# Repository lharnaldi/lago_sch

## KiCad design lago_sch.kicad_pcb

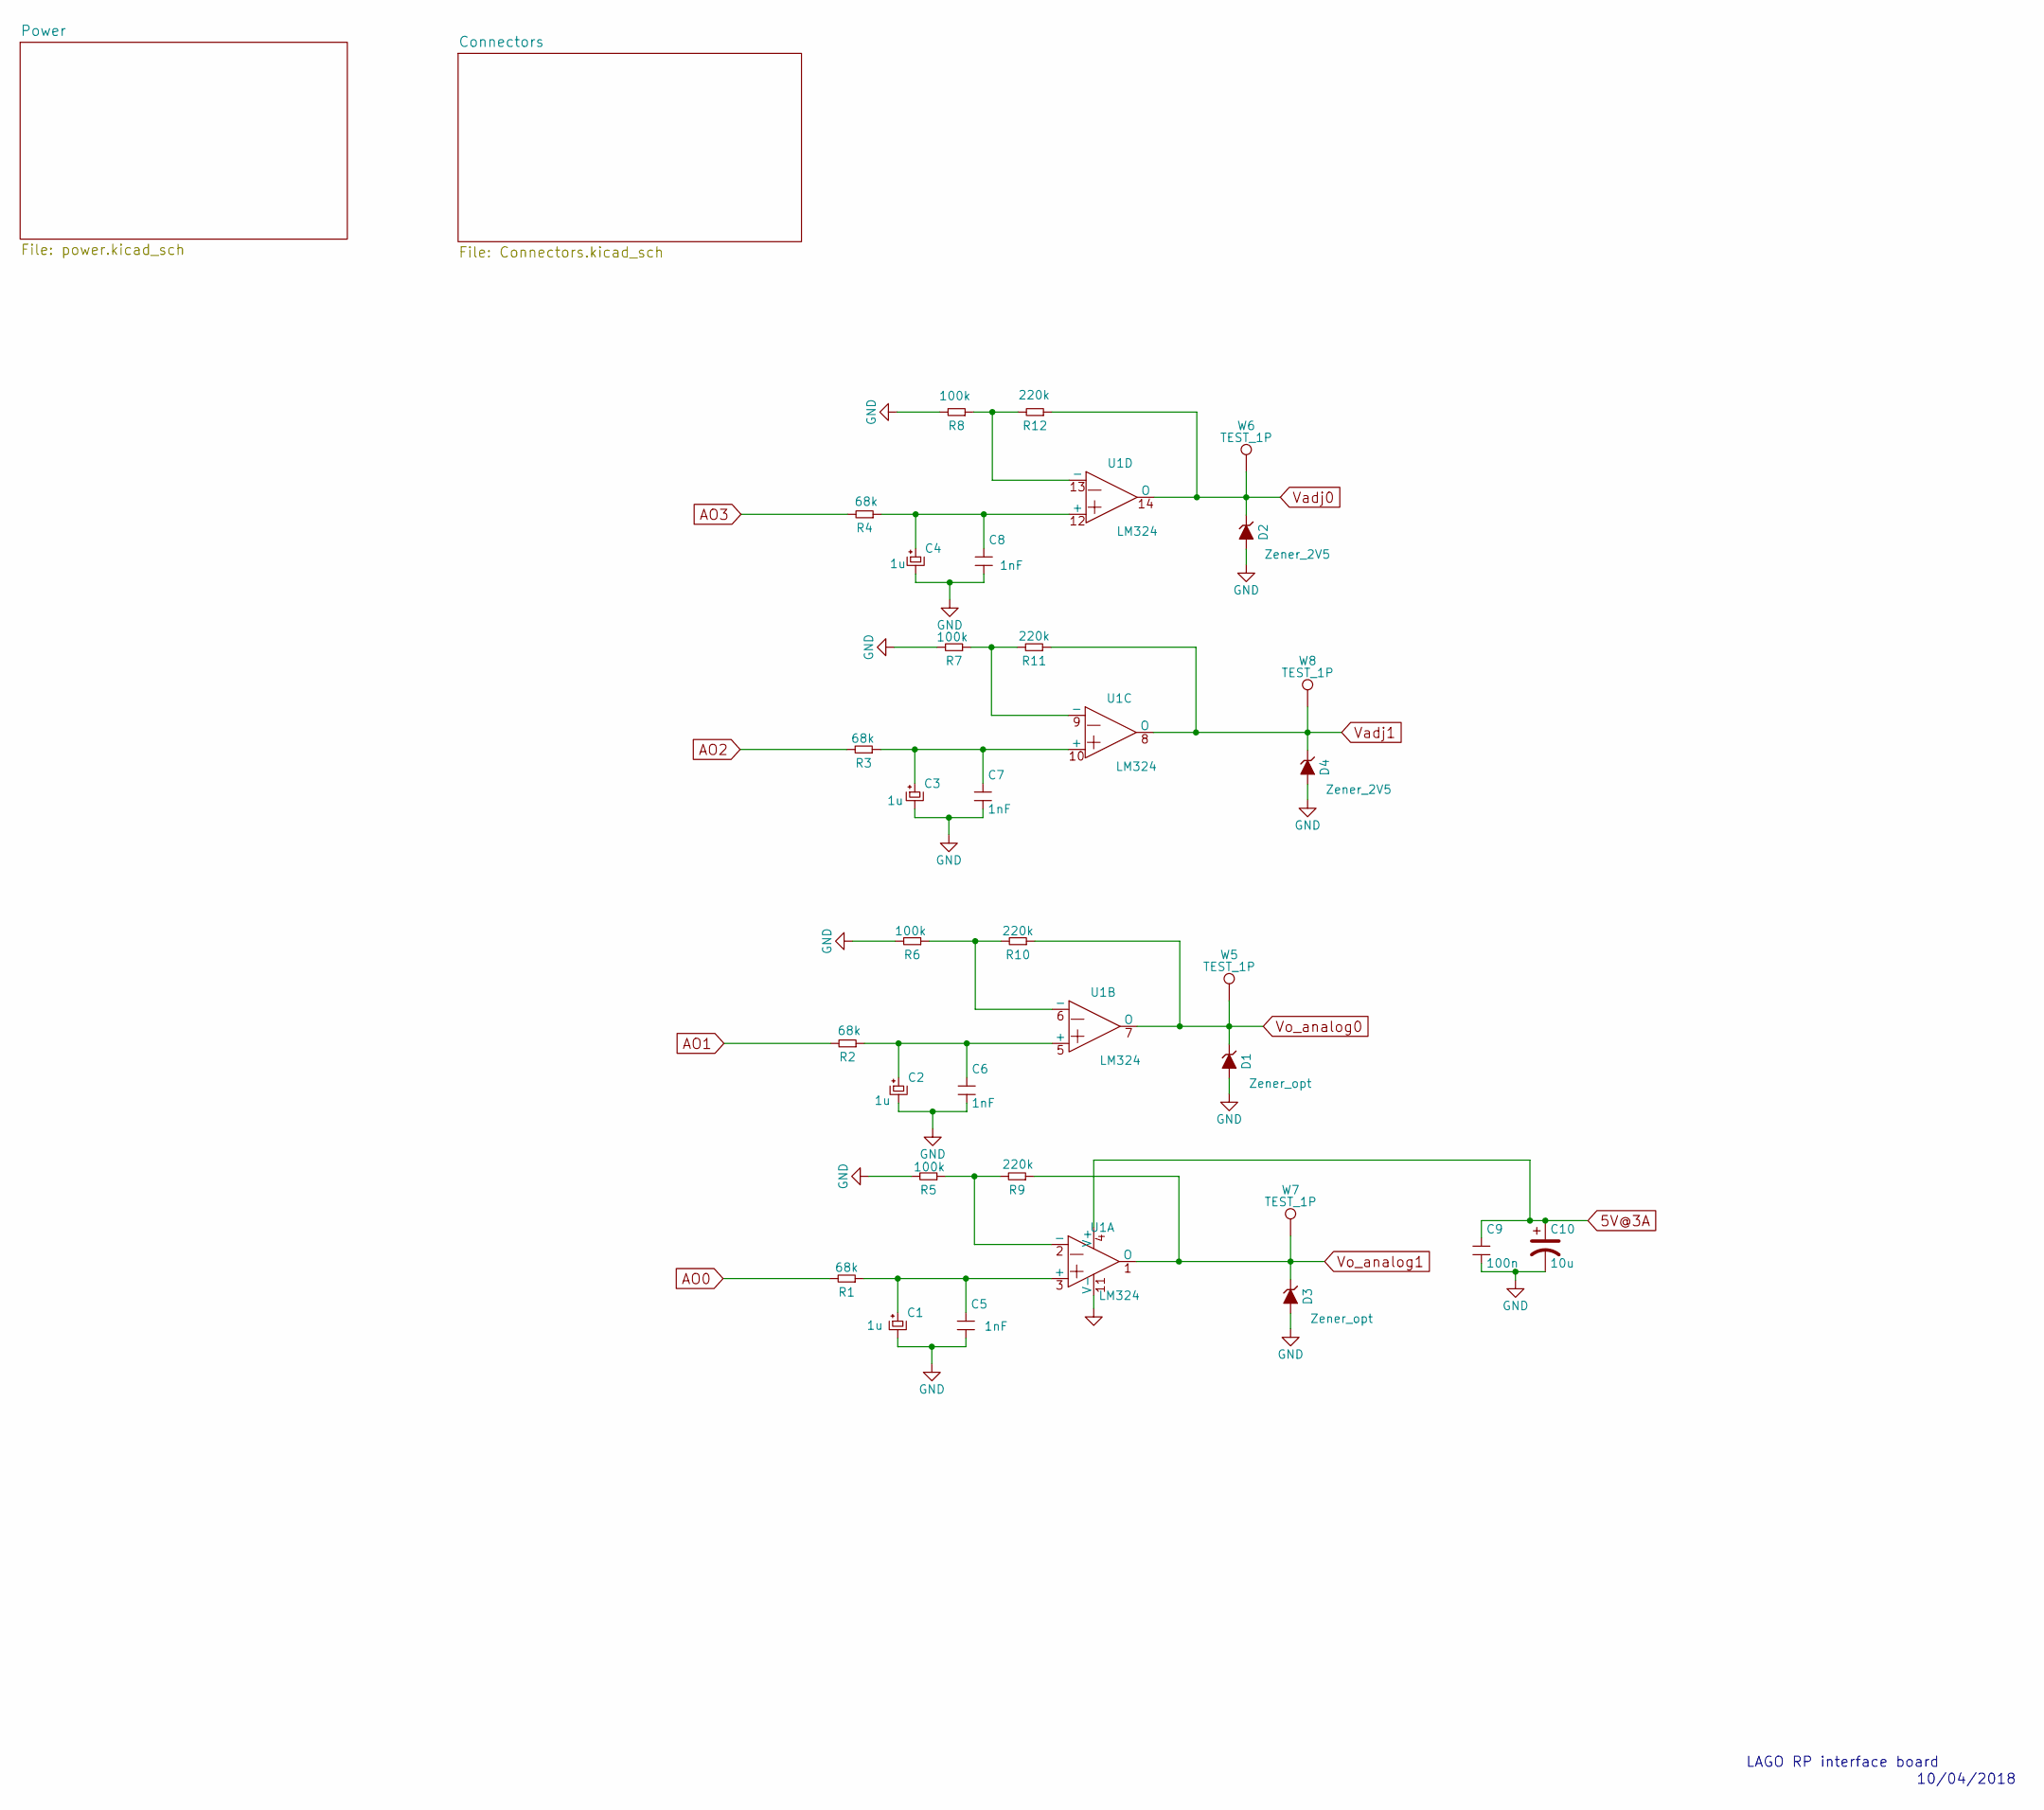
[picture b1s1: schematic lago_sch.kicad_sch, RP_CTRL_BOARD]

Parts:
C1, C2, C3, C4: 1u; c_0805
C5, C6, C7, C8: 1nF; c_0805
C9: 100n; c_0805
C10: 10u; C_1812_HandSoldering
D1, D3: Zener_opt; sod123
D2, D4: Zener_2V5; sod123
R1, R2, R3, R4: 68k; R_0805_HandSoldering
R5, R6, R7, R8: 100k; R_0805_HandSoldering
R9, R10, R11, R12: 220k; R_0805_HandSoldering
U1: LM324; SOIC-14_N
W5, W6, W7, W8: TEST_1P; Measurement_Point_Round-SMD-Pad_Small

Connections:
5V@3A: C9.1, C10.1, U1.4 (V+); also elsewhere on the board
AO0: R1.2; also elsewhere on the board
AO1: R2.2; also elsewhere on the board
AO2: R3.2; also elsewhere on the board
AO3: R4.2; also elsewhere on the board
GND: C1.2, C2.2, C3.2, C4.2, C5.2, C6.2, C7.2, C8.2, C9.2, C10.2, D1.2 (A), D2.2 (A), D3.2 (A), D4.2 (A), R5.2, R6.2, R7.2, R8.2, U1.11 (V-); also elsewhere on the board
unnamed: C1.1, C5.1, R1.1, U1.3 (+)
unnamed: C2.1, C6.1, R2.1, U1.5 (+)
unnamed: C3.1, C7.1, R3.1, U1.10 (+)
unnamed: C4.1, C8.1, R4.1, U1.12 (+)
unnamed: R5.1, R9.2, U1.2 (-)
unnamed: R6.1, R10.2, U1.6 (-)
unnamed: R7.1, R11.2, U1.9 (-)
unnamed: R8.1, R12.2, U1.13 (-)
Vadj0: D2.1 (K), R12.1, U1.14 (O), W6.1; also elsewhere on the board
Vadj1: D4.1 (K), R11.1, U1.8 (O), W8.1; also elsewhere on the board
Vo_analog0: D1.1 (K), R10.1, U1.7 (O), W5.1; also elsewhere on the board
Vo_analog1: D3.1 (K), R9.1, U1.1 (O), W7.1; also elsewhere on the board

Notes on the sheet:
10/04/2018
LAGO RP interface board

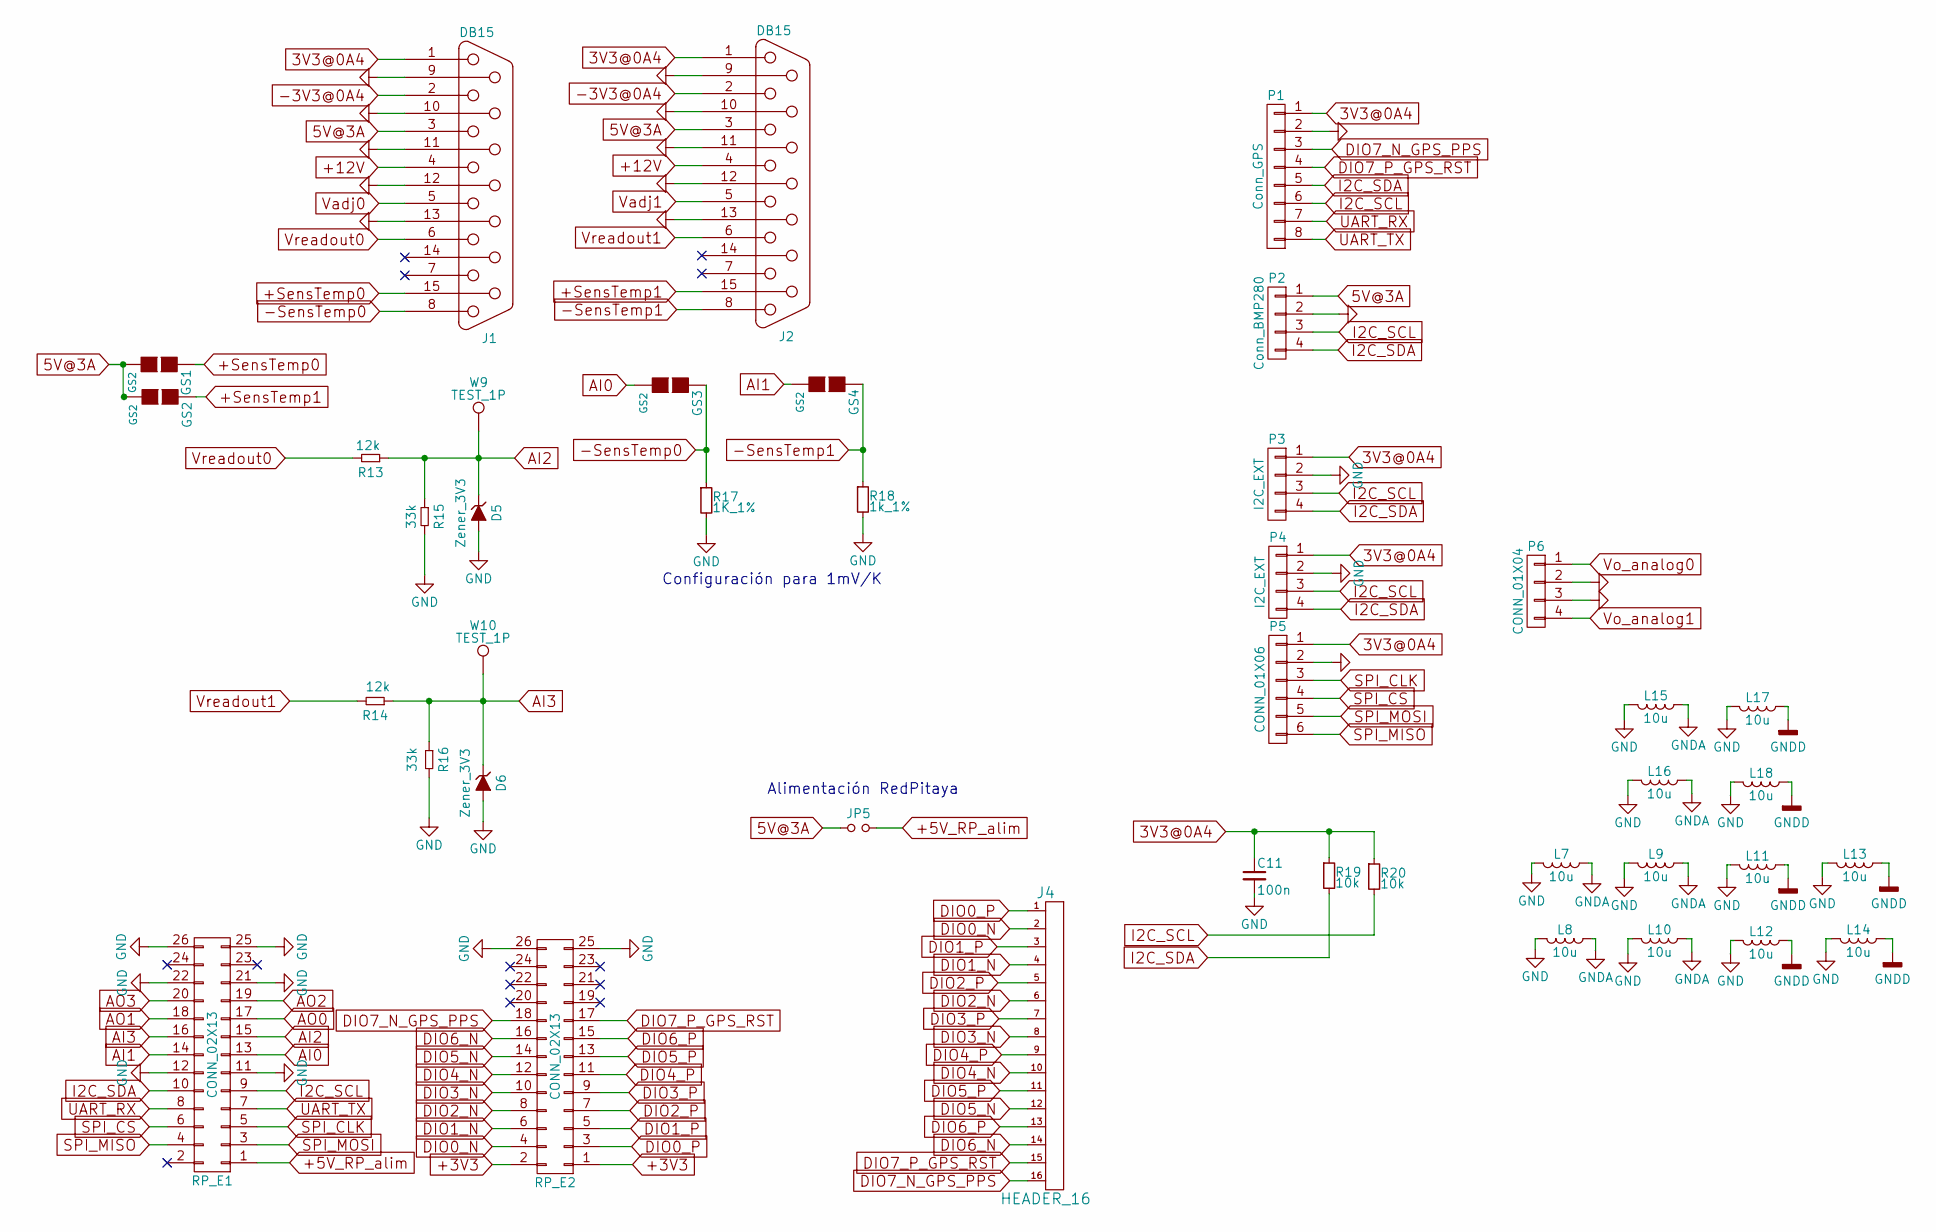
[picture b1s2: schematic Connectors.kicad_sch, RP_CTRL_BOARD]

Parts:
C11: 100n; c_0805
D5, D6: Zener_3V3; sod123
GS1, GS2, GS3, GS4: GS2
J1, J2: DB15; DB15MC
J4: HEADER_16; Pin_Header_Straight_1x16
JP5: Jumper_NO_Small; Pin_Header_Straight_1x02
L7, L8, L9, L10, L11, L12, L13, L14, L15, L16, L17, L18: 10u; Choke_SMD_1206_Standard
P1: Conn_GPS; Pin_Header_Straight_1x08
P2: Conn_BMP280; Pin_Header_Straight_1x04
P3, P4: I2C_EXT; Pin_Header_Straight_1x04
P5: CONN_01X06; Pin_Header_Straight_1x06
P6: CONN_01X04; Pin_Header_Straight_1x04
R13, R14: 12k; R_0805_HandSoldering
R15, R16: 33k; R_0805_HandSoldering
R17: 1K_1%; R_0805_HandSoldering
R18: 1k_1%; R_0805_HandSoldering
R19, R20: 10k; R_0805_HandSoldering
RP_E1, RP_E2: CONN_02X13; IDC_Header_Straight_26pins
W9, W10: TEST_1P; Measurement_Point_Round-SMD-Pad_Small

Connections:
3V3@0A4: C11.1, J1.1, J2.1, P1.1, P3.1, P4.1, P5.1, R19.1, R20.1; also elsewhere on the board
5V@3A: GS1.2 (G2), GS2.2 (G2), J1.3, J2.3, JP5.1, P2.1; also elsewhere on the board
+3V3: RP_E2.1, RP_E2.2
+5V_RP_alim: JP5.2, RP_E1.1
+12V: J1.4, J2.4; also elsewhere on the board
+SensTemp0: GS1.1 (G1), J1.15
+SensTemp1: GS2.1 (G1), J2.15
-3V3@0A4: J1.2, J2.2; also elsewhere on the board
-SensTemp0: GS3.1 (G1), J1.8, R17.1
-SensTemp1: GS4.1 (G1), J2.8, R18.1
AI0: GS3.2 (G2), RP_E1.13
AI1: GS4.2 (G2), RP_E1.14
AI2: D5.1 (K), R13.1, R15.1, RP_E1.15, W9.1
AI3: D6.1 (K), R14.1, R16.1, RP_E1.16, W10.1
AO0: RP_E1.17; also elsewhere on the board
AO1: RP_E1.18; also elsewhere on the board
AO2: RP_E1.19; also elsewhere on the board
AO3: RP_E1.20; also elsewhere on the board
DIO0_N: J4.2, RP_E2.4
DIO0_P: J4.1, RP_E2.3
DIO1_N: J4.4, RP_E2.6
DIO1_P: J4.3, RP_E2.5
DIO2_N: J4.6, RP_E2.8
DIO2_P: J4.5, RP_E2.7
DIO3_N: J4.8, RP_E2.10
DIO3_P: J4.7, RP_E2.9
DIO4_N: J4.10, RP_E2.12
DIO4_P: J4.9, RP_E2.11
DIO5_N: J4.12, RP_E2.14
DIO5_P: J4.11, RP_E2.13
DIO6_N: J4.14, RP_E2.16
DIO6_P: J4.13, RP_E2.15
DIO7_N_GPS_PPS: J4.16, P1.3, RP_E2.18
DIO7_P_GPS_RST: J4.15, P1.4, RP_E2.17
GND: C11.2, D5.2 (A), D6.2 (A), J1.9, J1.10, J1.11 (P111), J1.12, J1.13, J2.9, J2.10, J2.11 (P111), J2.12, J2.13, L7.2, L8.2, L9.2, L10.2, L11.2, L12.2, L13.2, L14.2, L15.2, L16.2, L17.2, L18.2, P1.2, P2.2, P3.2, P4.2, P5.2, P6.2, P6.3, R15.2, R16.2, R17.2, R18.2, RP_E1.11, RP_E1.12, RP_E1.21, RP_E1.22, RP_E1.25, RP_E1.26, RP_E2.25, RP_E2.26; also elsewhere on the board
GNDA: L7.1, L8.1, L9.1, L10.1, L15.1, L16.1; also elsewhere on the board
GNDD: L11.1, L12.1, L13.1, L14.1, L17.1, L18.1; also elsewhere on the board
I2C_SCL: P1.6, P2.3, P3.3, P4.3, R20.2, RP_E1.9
I2C_SDA: P1.5, P2.4, P3.4, P4.4, R19.2, RP_E1.10
SPI_CLK: P5.3, RP_E1.5
SPI_CS: P5.4, RP_E1.6
SPI_MISO: P5.6, RP_E1.4
SPI_MOSI: P5.5, RP_E1.3
UART_RX: P1.7, RP_E1.8
UART_TX: P1.8, RP_E1.7
Vadj0: J1.5; also elsewhere on the board
Vadj1: J2.5; also elsewhere on the board
Vo_analog0: P6.1; also elsewhere on the board
Vo_analog1: P6.4; also elsewhere on the board
Vreadout0: J1.6, R13.2
Vreadout1: J2.6, R14.2

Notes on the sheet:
Configuración para 1mV/K
Alimentación RedPitaya

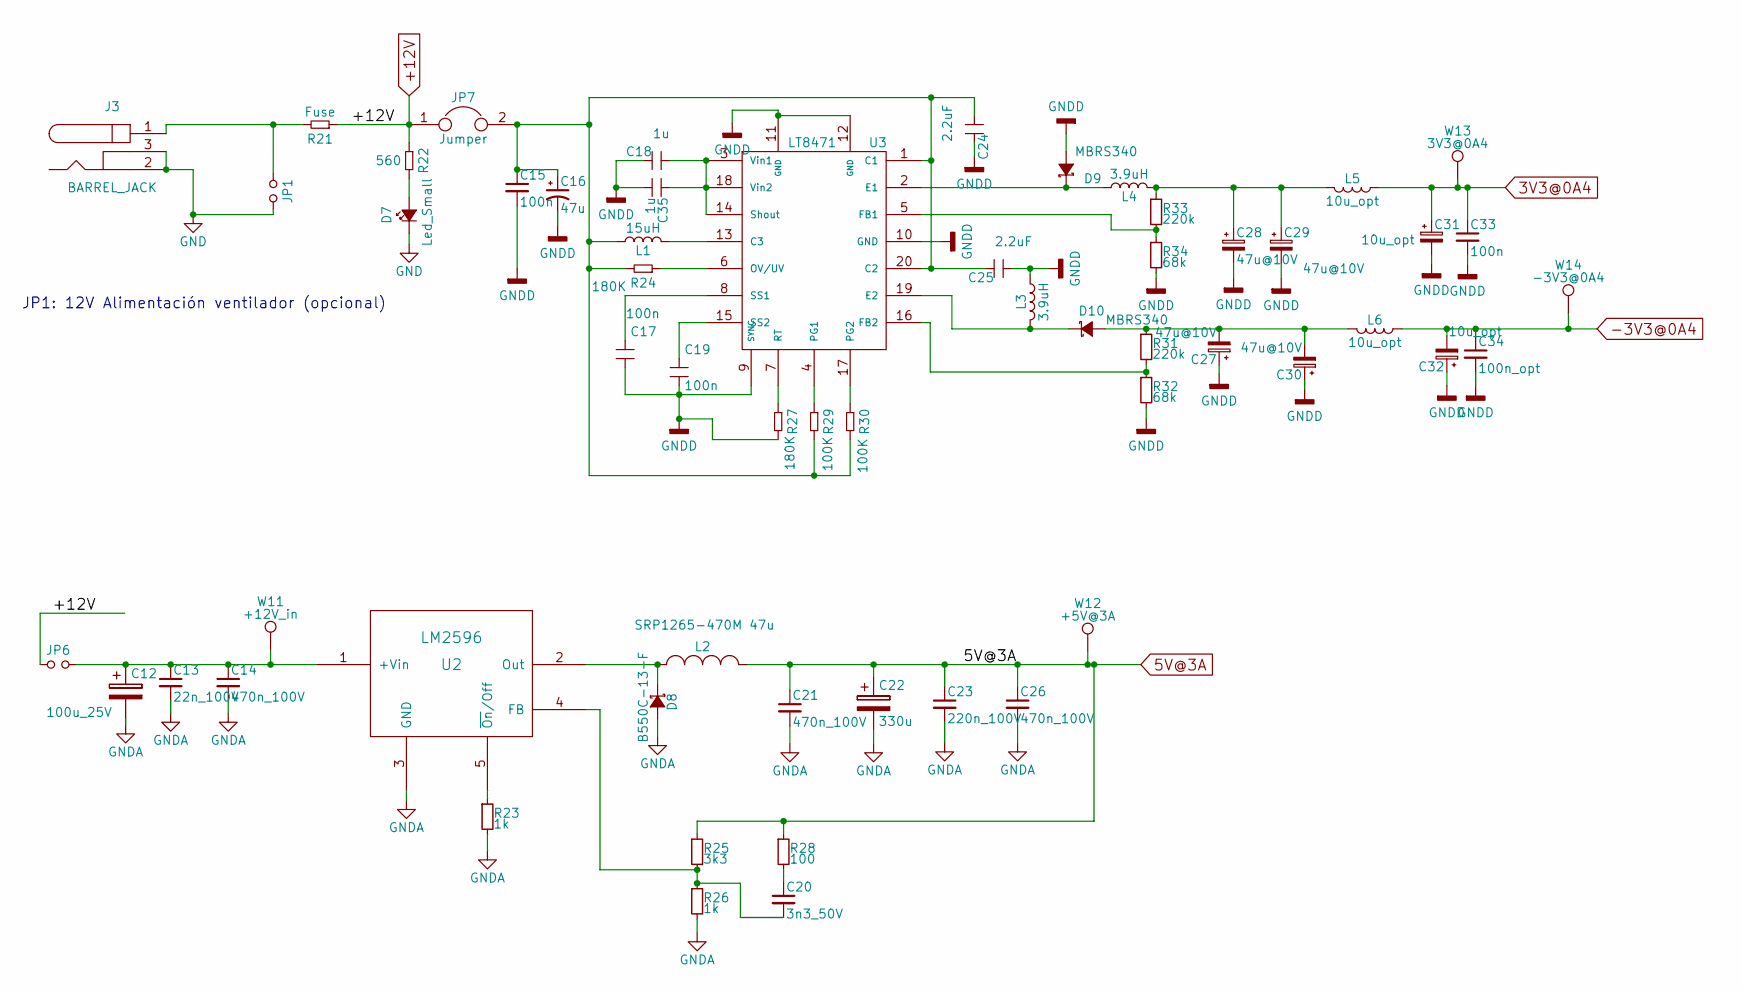
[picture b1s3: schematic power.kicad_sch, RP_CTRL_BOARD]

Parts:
C12: 100u_25V; C_Radial_D6.3_L11.2_P2.5
C13: 22n_100V; c_0805
C14, C21, C26: 470n_100V; c_0805
C15, C17, C19, C33: 100n; c_0805
C16: 47u; C_Radial_D6.3_L11.2_P2.5
C18, C35: 1u; c_0805
C20: 3n3_50V; c_0805
C22: 330u; C_Radial_D10_L16_P5
C23: 220n_100V; c_0805
C24, C25: 2.2uF; c_1206
C27, C28, C29, C30: 47u@10V; C_Radial_D6.3_L11.2_P2.5
C31, C32: 10u_opt; C_1812_HandSoldering
C34: 100n_opt; c_0805
D7: Led_Small; sod123
D8: B550C-13-F; SMC_Standard
D9, D10: MBRS340; DO-214AB
J3: BARREL_JACK
JP1, JP6: Jumper_NO_Small; Pin_Header_Straight_1x02
JP7: Jumper; Pin_Header_Straight_1x02
L1: 15uH; Neosid_Inductor_SM-NE56_SMD2220
L2: SRP1265-470M 47u; SELF-WE-PD-XXL
L3, L4: 3.9uH; self_cms_we-tpc_XL
L5, L6: 10u_opt; Neosid_Inductor_SM1206
R21: Fuse; R_0805_HandSoldering
R22: 560; R_0805_HandSoldering
R23, R26: 1k; R_0805_HandSoldering
R24, R27: 180K; R_0805_HandSoldering
R25: 3k3; R_0805_HandSoldering
R28: 100; R_0805_HandSoldering
R29, R30: 100K; R_0805_HandSoldering
R31, R33: 220k; R_0805_HandSoldering
R32, R34: 68k; R_0805_HandSoldering
U2: LM2596; TO-263-5Lead
U3: LT8471; TSSOP-20_4.4x6.5mm_Pitch0.65mm
W11: +12V_in; Measurement_Point_Round-SMD-Pad_Small
W12: +5V@3A; Measurement_Point_Round-SMD-Pad_Small
W13: 3V3@0A4; Measurement_Point_Round-SMD-Pad_Small
W14: -3V3@0A4; Measurement_Point_Round-SMD-Pad_Small

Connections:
3V3@0A4: C31.1, C33.1, L5.1, W13.1; also elsewhere on the board
5V@3A: C21.1, C22.1, C23.1, C26.1, L2.2, R25.1, R28.1, W12.1; also elsewhere on the board
+12V: JP6.1, JP7.1, R21.1, R22.1; also elsewhere on the board
-3V3@0A4: C32.2, C34.1, L6.1, W14.1; also elsewhere on the board
GND: D7.1 (K), J3.2, J3.3, JP1.2; also elsewhere on the board
GNDA: C12.2, C13.2, C14.2, C21.2, C22.2, C23.2, C26.2, D8.2 (A), R23.2, R26.2, U2.3 (GND); also elsewhere on the board
GNDD: C15.2, C16.2, C17.2, C18.2, C19.2, C24.2, C25.1, C27.1, C28.2, C29.2, C30.1, C31.2, C32.1, C33.2, C34.2, C35.2, D9.2 (A), L3.1, R27.2, R32.2, R34.2, U3.9 (SYNC), U3.10 (GND), U3.11 (GND), U3.12 (GND); also elsewhere on the board
unnamed: C12.1, C13.1, C14.1, JP6.2, U2.1 (+Vin), W11.1
unnamed: C15.1, C16.1, C24.1, C25.2, JP7.2, L1.1, R24.2, R29.2, R30.2, U3.1 (C1), U3.20 (C2)
unnamed: C17.1, U3.8 (SS1)
unnamed: C18.1, C35.1, U3.3 (Vin1), U3.14 (Shout), U3.18 (Vin2)
unnamed: C19.1, U3.15 (SS2)
unnamed: C20.1, R28.2
unnamed: C20.2, R25.2, R26.1, U2.4 (FB)
unnamed: C27.2, C30.2, D10.2 (A), L6.2, R31.1
unnamed: C28.1, C29.1, L4.2, L5.2, R33.1
unnamed: D7.2 (A), R22.2
unnamed: D8.1 (K), L2.1, U2.2 (Out)
unnamed: D9.1 (K), L4.1, U3.2 (E1)
unnamed: D10.1 (K), L3.2, U3.19 (E2)
unnamed: J3.1, JP1.1, R21.2
unnamed: L1.2, U3.13 (C3)
unnamed: R23.1, U2.5 (~On/Off)
unnamed: R24.1, U3.6 (OV/UV)
unnamed: R27.1, U3.7 (RT)
unnamed: R29.1, U3.4 (PG1)
unnamed: R30.1, U3.17 (PG2)
unnamed: R31.2, R32.1, U3.16 (FB2)
unnamed: R33.2, R34.1, U3.5 (FB1)

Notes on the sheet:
JP1: 12V Alimentación ventilador (opcional)

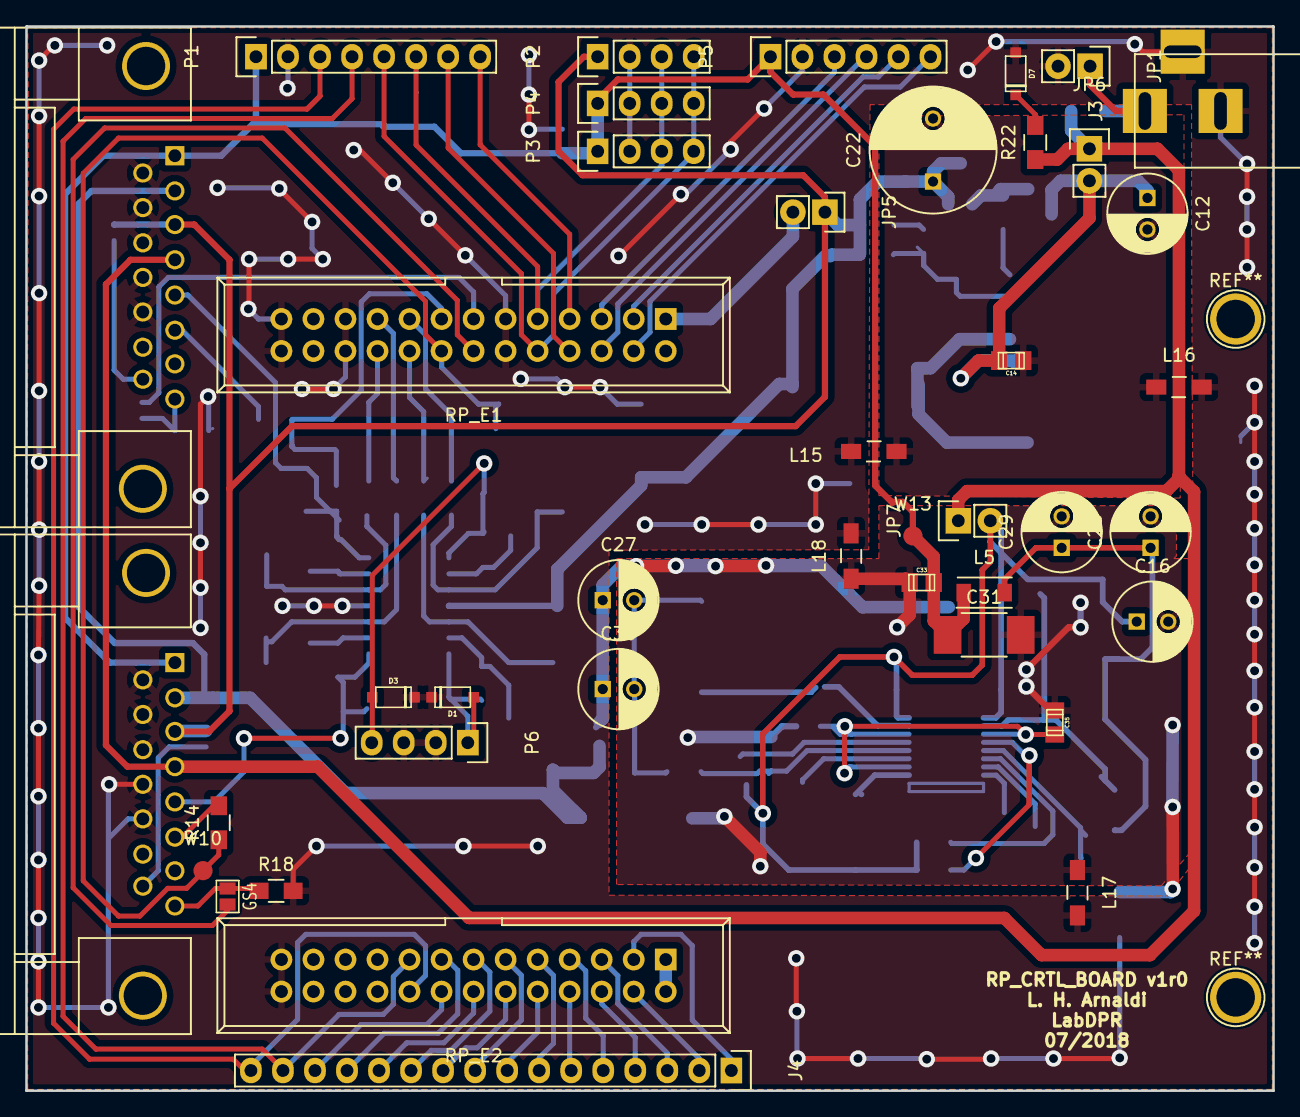
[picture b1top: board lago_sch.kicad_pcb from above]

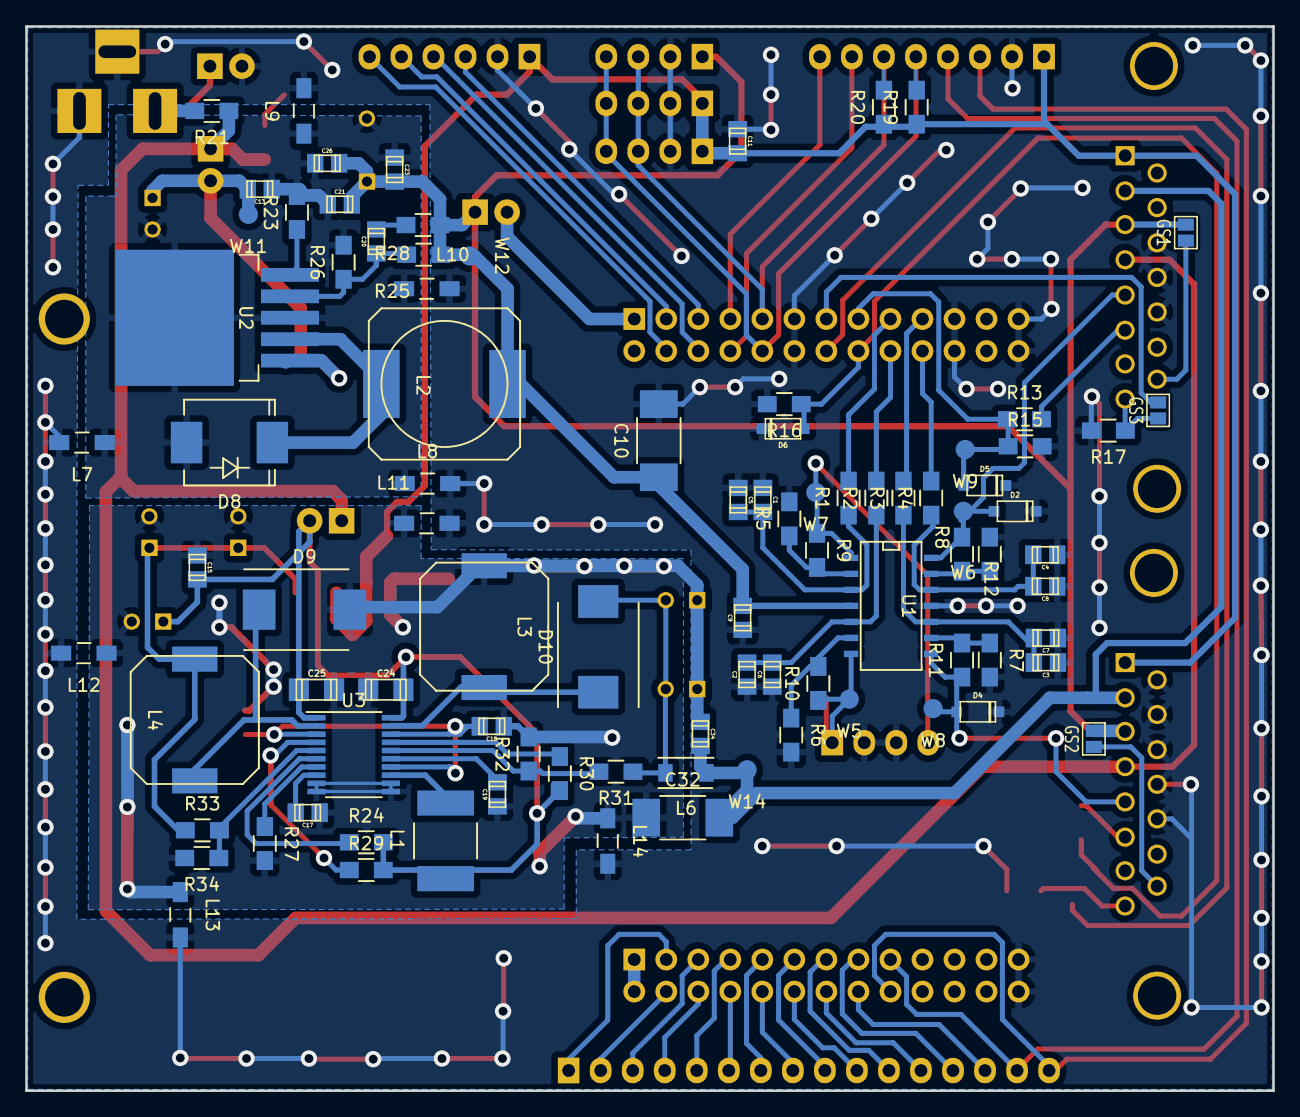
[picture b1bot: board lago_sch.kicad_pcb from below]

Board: 2 copper layers, 98.9 x 84.4 mm, 130 parts (89 on the bottom side), 81 nets.

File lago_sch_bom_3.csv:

Component,Description,Part,References,Value,Footprint,Quantity Per PCB,Datasheet
1,,C,C9 C11 C15 C17 C19 C33,100n,c_0805,6,
2,,C_Small,C34,100n_opt,c_0805,1,
3,,CP,C12,100u_25V,C_Radial_D6.3_L11.2_P2.5,1,
4,,CP1,C10,10u,C_1812_HandSoldering,1,
5,,CP_Small,C31 C32,10u_opt,C_1812_HandSoldering,2,
6,,C,C5 C6 C7 C8,1nF,c_0805,4,
7,,cap,C1 C2 C3 C4 C18 C35,1u,c_0805,6,
8,,C,C24 C25,2.2uF,c_1206,2,
9,,C_Small,C23,220n_100V,c_0805,1,
10,,C_Small,C13,22n_100V,c_0805,1,
11,,CP,C22,330u,C_Radial_D10_L16_P5,1,
12,,C_Small,C20,3n3_50V,c_0805,1,
13,,C_Small,C14 C21 C26,470n_100V,c_0805,3,
14,,CP1_Small,C16,47u,C_Radial_D6.3_L11.2_P2.5,1,
15,,CP_Small,C27 C28 C29 C30,47u@10V,C_Radial_D6.3_L11.2_P2.5,4,
16,,D_Schottky_Small,D8,B550C-13-F,SMC_Standard,1,
17,,Led_Small,D7,Led_Small,sod123,1,
18,,D_Schottky_Small_ALT,D9 D10,MBRS340,DO-214AB,2,
19,,ZENERsmall,D2 D4,Zener_2V5,sod123,2,
20,,ZENERsmall,D5 D6,Zener_3V3,sod123,2,
21,,ZENERsmall,D1 D3,Zener_opt,sod123,2,
22,,GS2,GS1 GS2 GS3 GS4,GS2,GS2,4,
23,,BARREL_JACK,J3,BARREL_JACK,BARREL_JACK,1,
24,,DB15,J1 J2,DB15,DB15MC,2,
25,,HEADER_16,J4,HEADER_16,Pin_Header_Straight_1x16,1,
26,,Jumper,JP7,Jumper,Pin_Header_Straight_1x02,1,
27,,Jumper_NO_Small,JP1 JP5 JP6,Jumper_NO_Small,Pin_Header_Straight_1x02,3,
28,,L,L7 L8 L9 L10 L11 L12 L13 L14 L15 L16 L17 L18,10u,Choke_SMD_1206_Standard,12,
29,,L,L5 L6,10u_opt,Neosid_Inductor_SM1206,2,
30,,L,L1,15uH,Neosid_Inductor_SM-NE56_SMD2220,1,
31,,L,L3 L4,3.9uH,self_cms_we-tpc_XL,2,
32,,INDUCTOR_SMALL,L2,SRP1265-470M 47u,SELF-WE-PD-XXL,1,
33,,CONN_01X04,P6,CONN_01X04,Pin_Header_Straight_1x04,1,
34,,CONN_01X06,P5,CONN_01X06,Pin_Header_Straight_1x06,1,
35,,CONN_01X04,P2,Conn_BMP280,Pin_Header_Straight_1x04,1,
36,,CONN_01X08,P1,Conn_GPS,Pin_Header_Straight_1x08,1,
37,,CONN_01X04,P3 P4,I2C_EXT,Pin_Header_Straight_1x04,2,
38,,R_Small,R28,100,R_0805_HandSoldering,1,
39,,R,R5 R6 R7 R8 R29 R30,100k,R_0805_HandSoldering,6,
40,,R_Small,R19 R20,10k,R_0805_HandSoldering,2,
41,,R,R13 R14,12k,R_0805_HandSoldering,2,
42,,R,R24 R27,180K,R_0805_HandSoldering,2,
43,,R_Small,R17 R18,1K_1%,R_0805_HandSoldering,2,
44,,R_Small,R23 R26,1k,R_0805_HandSoldering,2,
45,,R,R9 R10 R11 R12 R31 R33,220k,R_0805_HandSoldering,6,
46,,R,R15 R16,33k,R_0805_HandSoldering,2,
47,,R_Small,R25,3k3,R_0805_HandSoldering,1,
48,,R,R22,560,R_0805_HandSoldering,1,
49,,R,R1 R2 R3 R4 R32 R34,68k,R_0805_HandSoldering,6,
50,,R,R21,Fuse,R_0805_HandSoldering,1,
51,,CONN_02X13,RP_E1 RP_E2,CONN_02X13,IDC_Header_Straight_26pins,2,
52,,LM2596,U2,LM2596,TO-263-5Lead,1,
53,,LM324,U1,LM324,SOIC-14_N,1,
54,,LT8471,U3,LT8471,TSSOP-20_4.4x6.5mm_Pitch0.65mm,1,
55,,TEST_1P,W11,+12V_in,Measurement_Point_Round-SMD-Pad_Small,1,
56,,TEST_1P,W12,+5V@3A,Measurement_Point_Round-SMD-Pad_Small,1,
57,,TEST_1P,W14,-3V3@0A4,Measurement_Point_Round-SMD-Pad_Small,1,
58,,TEST_1P,W13,3V3@0A4,Measurement_Point_Round-SMD-Pad_Small,1,
59,,TEST_1P,W5 W6 W7 W8 W9 W10,TEST_1P,Measurement_Point_Round-SMD-Pad_Small,6,





Component Groups:,59
Component Count:,130
Fitted Components:,130
Number of PCBs:,1
Total components:,130
Schematic Version:,3
Schematic Date:,07/2018
BoM Date:,vie 13 dic 2019 12:19:26 -03
Schematic Source:,/home/arnaldi/work/mercurialrepos/lharnaldi/kicad/lago_sch/lago_sch.sch
KiCad Version:,Eeschema 5.0.2-bee76a0~70~ubuntu18.04.1

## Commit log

2020-01-29 Primer commit de este repositorio. Copia de lago_sch de mercurial.
2022-03-14 Agrgeo la version para kicad v6
2022-03-14 Agrego el gitignore
2022-03-14 Agrego la version modificada para Mario de Ecuador, con vias mas grandes
2022-03-14 Remuevo archivos que ya no se usan en kicad v6
2022-08-04 Actualicé el pcb con los valores del esquemático
